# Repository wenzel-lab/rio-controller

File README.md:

# "Rio" the modular microfluidics controller 

This repository contains the _free_ and _open-source_ designs and documentation for the _core board_ and their _modules_ of a microfluidics workstation to enable _high-throughput droplet microfluidic_ biological assays. The designs contain an electronics board "hat" that plugs onto a Raspberry Pi single-board computer and interfaces with our _compact controllers_ e.g. for gas-pressure control to push microfluidic samples onto chips, pressure, and flow measurement with feedback control, sample holders with heating and stirring, and imaging of fast droplet generation processes with open-source microscopy and stroboscopic illumination.

This is an open, collaborative project by the [Wenzel Lab](https://wenzel-lab.github.io/en/) in Chile, and _your participation_ (comments, inputs, contributions) are explicitly welcome! Please submit your message as an issue in this repository to participate.

Follow us! [#twitter](https://twitter.com/WenzelLab), [#YouTube](https://www.youtube.com/@librehub), [#LinkedIn](https://www.linkedin.com/company/92802424), [#instagram](https://www.instagram.com/wenzellab/), [#Printables](https://www.printables.com/@WenzelLab), [#LIBREhub website](https://librehub.github.io), [#IIBM website](https://ingenieriabiologicaymedica.uc.cl/en/people/faculty/821-tobias-wenzel)

## Table of contents

- [Why](#why)
- [Getting Started](#getting-started)
- [Use Cases](#use-cases)
- [Read the Paper](#read-the-paper)
- [Modules Wish List](#modules-wish-list)
- [Contributing](#contributing)
- [License](#license)

## Why

Our aim is to create a prototype of a _compact_ working station for microfluidic research that is based on _connectable_, _open_, modern, and _low-cost_ components (Rasberry Pi, Arduino, 3D printing, on-board components, open or at least accessible design software and operation software - python).

**Rio** serves as a platform to implement fully functional research-grade workstations with good specifications, such as fast reaction times and low-pressure fluctuations. It is modular so that parts of this platform can be repurposed and improved in the open-source hardware sense and easily combined, exchanged, or used independently in challenging environments.

## Getting Started

For a repository architecture guide, see [ARCHITECTURE.md](ARCHITECTURE.md)
- **Software (runtime + development)**: [`software/README.md`](software/README.md)
  - Main entry point: `software/main.py`
- **Deployment bundle (Pi updates)**: generated via `scripts/deploy/create-pi-deployment.sh` into `pi-deployment/`
- **Hardware modules** (assembly + usage):
  - Pi HAT: [`hardware-modules/rpi-hat/README.md`](hardware-modules/rpi-hat/README.md)
  - Strobe imaging: [`hardware-modules/strobe-imaging/README.md`](hardware-modules/strobe-imaging/README.md)
  - Pressure/flow: [`hardware-modules/pressure-flow-control/README.md`](hardware-modules/pressure-flow-control/README.md)
  - Heating/stirring: [`hardware-modules/heating-stirring/README.md`](hardware-modules/heating-stirring/README.md)

In order to implement a workstation, you must build the core board and any module of your interest. The user interface software will allow you to control and monitor the operations of the modules.

### Core Board

The core board consists of a Raspberry Pi 4B+ and a custom Pi HAT (hardware attached to the top). The Pi HAT is an extension board for bidirectional communication and power supply to the controllers. 

<table>
<tr>
    <td align="center"><b>Core Board</b></td>
</tr>
<tr>
    <td align="center"></td>
</tr>
<tr>
    <td align="center"><a href="hardware-modules/rpi-hat/"><br><b>Build the Pi HAT</b></a><br><br></td>
</tr>
</table>

### Modules

A _module_ commonly consists of a compact controller, sensors, and actuators, and operates with distinct power supply and data connections. The controllers convert physical data into digital data, manipulate the actuators, and supply energy to external components. 

<table>
<tr>
    <td align="center"><b>Strobe Imaging Module</b></td>
    <td align="center"><b>Pressure and Flow Control Module</b></td>
    <td align="center"><b>Heat and Stirring Module</b></td>
</tr>
<tr>
    <td align="center"></td>
    <td align="center"></td>
    <td align="center"></td>
</tr>
<tr>
    <td align="center"><a href="hardware-modules/strobe-imaging/"><br><b>Build the controller</b></a><br><br></td>
    <td align="center"><a href="hardware-modules/pressure-flow-control/"><br><b>Build the controller</b></a><br><br></td>
    <td align="center"><a href="hardware-modules/heating-stirring/"><br><b>Build the controller</b></a><br><br></td>
</tr>
</table>

### Software

The software follows a client-server architecture and allows users to control the physical hardware through a graphical interface. It runs on a Raspberry Pi (legacy 32-bit OS for Pi camera support).

**Installation and Usage:**
- For detailed software installation and usage instructions, see [software/README.md](software/README.md)

**Features:**
- Real-time camera control with strobe synchronization
- Droplet detection with histogram visualization
- Flow and pressure control
- Temperature and stirring control
- Modern web-based user interface

**How the software is structured (high level):**
- UI + routes: `software/rio-webapp/` (browser + Flask + Socket.IO)
- WebSocket handlers: `software/rio-webapp/controllers/`
- Device orchestration: `software/controllers/`
- Hardware adapters: `software/drivers/` (camera backends in `software/drivers/camera/`)
- Droplet detection pipeline: `software/droplet-detection/`

### Choose Your Scenario

- **Scenario 1 — Pi image (UI on Pi, optional API)**: Flask UI autostarts on the Pi, API is optional.
- **Scenario 2 — Pi API-only + external UI/camera**: Pi exposes API for Pi-HAT modules; external computer runs UI + image processing.
- **Scenario 2b — Pi API-only + Pi camera via API**: legacy `picamera` remains on the Pi; clients control via API.

For Pi mode switching, use `scripts/pi/rio-mode` (UI vs API single-owner).

## Use Cases

**Single-module solution:**
* Strobe-enhanced microscopy stage ([Repository](https://github.com/wenzel-lab/strobe-enhanced-microscopy-stage) | [Assembly Instructions](https://wenzel-lab.github.io/strobe-enhanced-microscopy-stage/))

**Three-modules solution:**
* Flow microscopy platform ([Repository](https://github.com/wenzel-lab/flow-microscopy-platform) | Assembly Instructions (Soon))

## Read the Paper

"Rio" has been employed in the article ["Plasmid Stability Analysis with Open-Source Droplet Microfluidics"](https://app.jove.com/t/67659/plasmid-stability-analysis-with-open-source-droplet-microfluidics), published in JoVE in December 2024. Please cite this article when using our hardware system.

DOI: [https://dx.doi.org/10.3791/67659](https://dx.doi.org/10.3791/67659)

## Modules Wish List

* High-pressure source module to replace large gas bottles with a small soda CO2 bottle, developed in this [sub-repository](https://github.com/wenzel-lab/rio-controller/tree/master/module-high-pressure-source)
* Support for small piezo pumps
* Smart cultivation sleeves for vials, smaller and with OD-tracking - the V2 of our current sample holders and strirrers
* Microfluidic droplet sorting workstation driven by the droplet workstation tools is described [here](https://github.com/wenzel-lab/droplet-sorter-master/tree/main) (This is being developed in a separate repository).

## Contributing

Feel free to dive in! [Open an issue](https://github.com/wenzel-lab/rio-controller/issues/new).
For interactions in our team and with the community applies the [GOSH Code of Conduct](https://openhardware.science/gosh-2017/gosh-code-of-conduct/). If you want to get involved in our research, please see the [website of our team](https://wenzel-lab.github.io/en/).

## License

**Hardware:** All source files located in the `hardware-modules` directories (including firmware, PCB designs, and documentation) and documentation are released under the [CERN-OHL-W-2.0](https://ohwr.org/cern_ohl_w_v2.txt) license.

**Software:** The source codes located in the `software` directory are released under the [GPL-3.0](https://www.gnu.org/licenses/gpl-3.0.en.html) license.

© Tobias Wenzel, Christie Nel, and Pierre Padilla-Huamantinco. This project is Open-Source Hardware - please cite and acknowledge us when using the hardware or sharing modifications.

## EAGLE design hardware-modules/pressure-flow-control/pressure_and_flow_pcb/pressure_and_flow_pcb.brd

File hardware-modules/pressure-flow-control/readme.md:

## Pressure and flow controller module

This is the core piece of the workstation. 
This electronic controller module aims to regulate and distrbute the pressure (originating from the pressure source module) into the sample tubes, so that the samples (aqueous, gel pre-cursors and oils) flow onto the microfluidic chip and the collection reservoirs.
We regulate high pressure for ultra-high throughput agarose bead generation (several bar), in a smooth fashion that avoids pulsing, especially at steady state.
This controller consists of a custom circuit board that plugs into the Raspberry Pi hat, in addition to connectors for connecting external pressure controllers and flow sensors. Pressure and flow control are fully automatic.

The controller module can operate either in pressure control mode or flow control mode.  Flow control mode requires external flow sensors to be connected.  Once desired flow rates have been achieved and associated pressures are known, the experiment can be reproduced using only pressure control, without the need for expensive flow sensors.  Both modes require external pressure controllers to be connected.

The module contains a PIC microcontroller that communicates with the Raspberry Pi, controls the pressure controllers and reads back pressure and flow.  The pressure target is controlled using a digital-to-analogue converter and the actual pressure is read using an analogue-to-digital converter.  The flow controllers is read via a four channel I2C multiplexer.

### Where the firmware and software live (repo structure)

- **Module firmware (PIC, MPLAB X project)**: `pressure_and_flow_pic/`
  - Developer-oriented firmware notes: `pressure_and_flow_pic/README.md`
- **Host-side driver (Raspberry Pi)**: `software/drivers/flow.py` (`PiFlow`)
- **UI-facing controller wrapper**: `software/controllers/flow_web.py` (`FlowWeb`)
- **UI wiring (web app)**: `software/rio-webapp/` + `software/rio-webapp/controllers/flow_controller.py`

When auditing end-to-end behavior, the most direct call chain is:
browser UI → Socket.IO `"flow"` handler → `FlowWeb` → `PiFlow` → `pressure_and_flow_pic/` firmware.

### Pressure Controllers
We have selected the SMC ITV0010 pressure controllers for this application.  The pressure target is supplied to the pressure controller by the module as an analogue voltage and the measured pressure achieved is returned as an analogue voltage.  This approach allows the option to connect alternative analogue pressure controllers, or using a separate pressure sensor instead of the one internal to the pressure controller.

The ITV0010 pressure controllers can be purchased as a compact DIN-mounted manifold block that requires a single pressure supply line.

### Flow Sensors
We have selected the Sensirion LG16 range of flow sensor.  They feature a digital interface via I2C.

### Connectors

The module features eight Picoblade connectors.  Four connect to the pressure controllers, carrying power, analogue out and analogue in.  The other four connect to the optional flow sensors and carry power and I2C signals.  The module itself is designed to plug into the Raspberry Pi hat.  This allows for power and digital communications with the Raspberry Pi.

#### Pressure Controller Connector

|Pin|Description|
|-|-|
|1|Pressure In|
|2|Pressure Out|
|3|0V Power / GND|
|4|12V Power|

#### Flow Sensor Connector

|Pin|Description|
|-|-|
|1|I2C Data|
|2|Vdd 3.3V|
|3|Vss (Digital Ground)|
|4|I2C Clock|

**Note:** Pin 2 (Vdd 3.3V) must not be used to power Sensirion LG16 sensors, which require 5V.  This 3.3V pin was intended for use with the Sensirion SLF3S-1300F.  Instead use the 5V pin on the Controller Module header block on the Raspberry Pi hat.

### Pinout

|Pin|Description|
|-|-|
|1|ICSP MCLR|
|2|ICSP Vdd (3V3 Power)|
|3|ICSP Vss (Digital Ground)|
|4|ICSP Data|
|5|ICSP Clock|
|13|Ground for 12V|
|14|12V Supply for Pressure Controllers|
|17|5V Digital Power|
|23|Digital Ground|
|24|Digital 3.3V Power|
|25|SPI Slave Select|
|26|SPI Clock|
|27|SPI MOSI|
|28|SPI MISO|

**Note:** Pin 13 (12V Ground) must be connected with pin 23 (digital ground) externally, and in a way that prevents ground loops.

### PCB Components

|Qty|Name|Component|Description|
|-|-|-|-|
|7|C1-C5,C8-C9|100nf Capacitor 0603|Decoupling Capacitors|
|2|C6,C10|10uF Capacitor 0603|Bypass,Bulk Capacitor|
|1|C7|Not fitted||
|1|IC2|dsPIC33CK256MP502-I/SS SSOP28|PIC Microprocessor|
|1|IC3|AD5624R|DAC|
|1|IC4|ADS1115|ADC|
|1|IC5|PCA9544APW,112|I2C Multiplexer|
|1|IC6|25AA040ST|EEPROM|
|12|R1-R10,R12-R13|1k Resistor 0603||
|1|R11|10k Resistor 0603||
|8|X1-X8|Picoblade 53047-0410|Connectors|

Please note that our current implementation is based on compact, low-cost and scalable PIC microcontrollers that fit onto the Pi-hat modules. These cannot simply be programmed with a micro-USB cables. Instead, they need an [additional small hardware ICSP interface](https://www.digikey.com/en/product-highlight/m/microchip-technology/pickit-3-in-circuit-debugger-programmer) (or equivalent) to load new code onto the PIC microcontrollers.

### Cable for Sensirion LG16

Flow Controller Module End

Connector Type: Picoblade 1.25mm 4-way (51021-0400)<br/>
Connector Crimps: Picoblade 26-28 AWG (50079-8000)

|Pin|Wire|Function|
|-|-|-|
|1|1|I2C Data|
|2|-|Not Connected|
|3|3|VSS|
|4|4|I2C Clock|

Connector Type: DuPont Standard Female

|Pin|Wire|Function|
|-|-|-|
|1|2|VDD 5V|

Flow Sensor End (Sensirion LG16)

Connector Type: Picoblade 1.25mm 5-way (51021-0500)<br/>
Connector Crimps: Picoblade 26-28 AWG (50079-8000)

|Pin|Wire|Function|
|-|-|-|
|1|1|I2C Data|
|2|4|I2C Clock|
|3|2|VDD 5V|
|4|3|VSS|
|5|-|Not Connected|

### Cable for SMC ITV Electro-Pneumatic Regulator

This cable was purchased from bpx.co.uk and a Picoblade connector fitted, which plugs into the Flow Controller Module.  The wires are too thick to fit directly into the crimps, so thinner wires must be soldered onto the cable.

Cable: M84DSX3MG4<br/>
Connector Type: Picoblade 1.25mm 4-way (51021-0400)<br/>
Connector Crimps: Picoblade 26-28 AWG (50079-8000)

|Pin|Colour|Function|
|-|-|-|
|1|Black|Input Signal|
|2|White|Monitor Output|
|3|Blue|GND (Common)|
|4|Brown|Power|

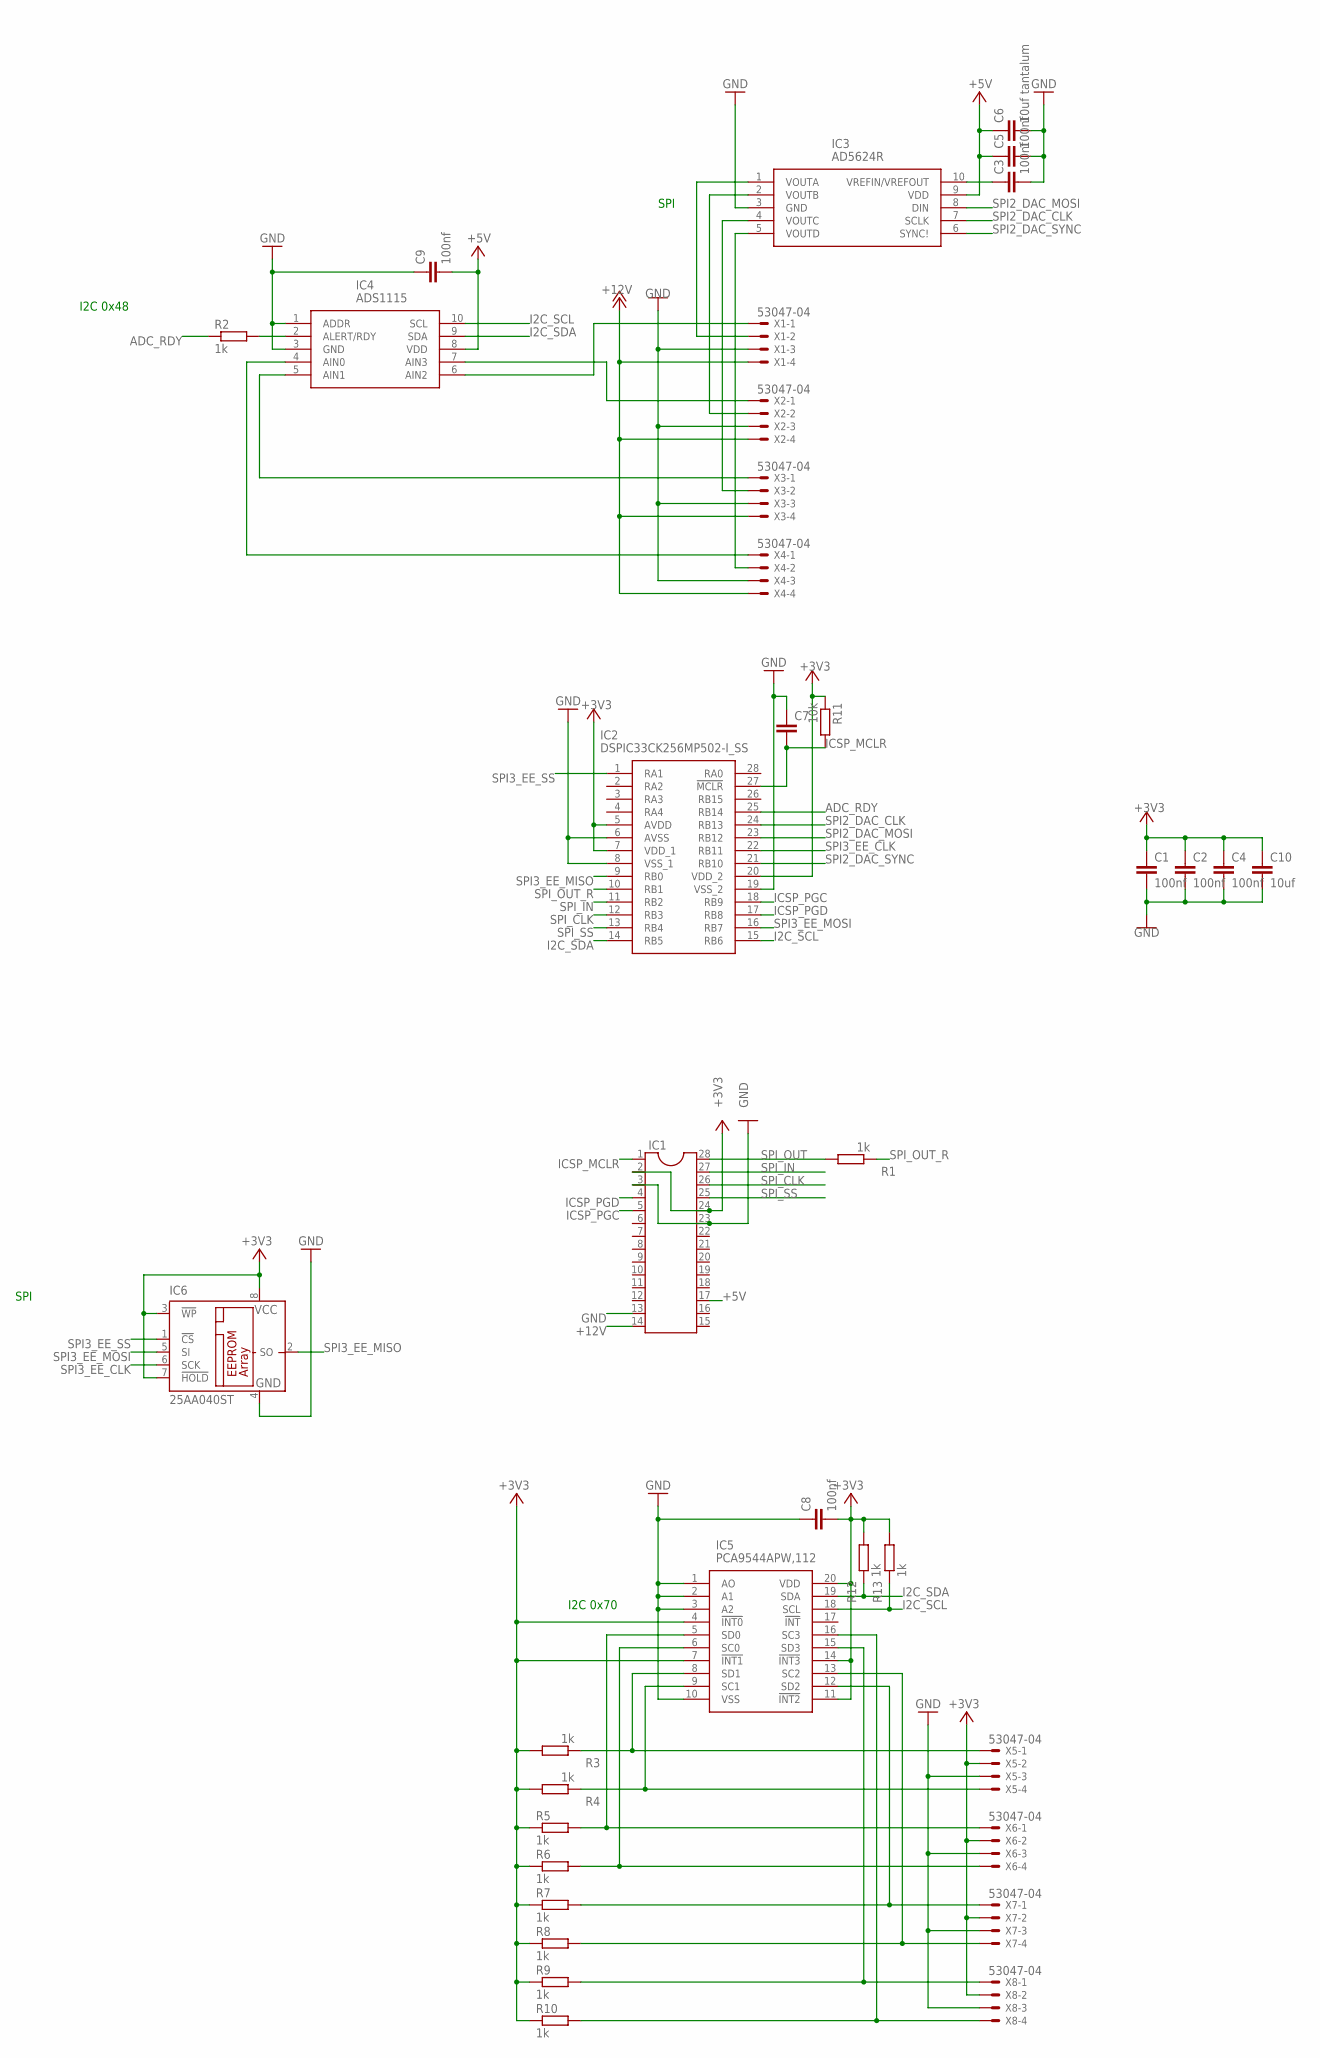
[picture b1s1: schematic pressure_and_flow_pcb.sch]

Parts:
C1, C2, C3, C4, C5, C8, C9: 100nf; C0603K
C6: 10uf tantalum; C0603K
C7: C-EUC0603K; C0603K
C10: 10uf; C0603K
IC1: DIL28; DIL28-6
IC2: DSPIC33CK256MP502-I_SS; SOP65P780X200-28N
IC3: AD5624R; SOP50P490X110-10N
IC4: ADS1115; SOP50P490X110-10N
IC5: PCA9544APW,112; SOP65P640X110-20N
IC6: 25AA040ST; TSSOP8
R1, R2, R3, R4, R5, R6, R7, R8, R9, R10, R12, R13: 1k; R0603
R11: 10k; R0603
X1, X2, X3, X4, X5, X6, X7, X8: 53047-04

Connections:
+3V3: C1.1, C2.1, C4.1, C8.2, C10.1, IC1.2, IC1.24, IC2.5 (AVDD), IC2.7 (VDD_1), IC2.20 (VDD_2), IC5.4 (!INT0), IC5.7 (!INT1), IC5.11 (!INT2), IC5.14 (!INT3), IC5.20 (VDD), IC6.3 (!WP), IC6.7 (!HOLD), IC6.8 (VCC), R3.2, R4.2, R5.1, R6.1, R7.1, R8.1, R9.1, R10.1, R11.1, R12.2, R13.2, X5.2, X6.2, X7.2, X8.2
+5V: C5.1, C6.1, C9.2, IC1.17, IC3.9 (VDD), IC4.8 (VDD)
+12V: IC1.14, X1.4, X2.4, X3.4, X4.4
ADC_RDY: IC2.25 (RB14), R2.1
GND: C1.2, C2.2, C3.2, C4.2, C5.2, C6.2, C7.1, C8.1, C9.1, C10.2, IC1.3, IC1.13, IC1.23, IC2.6 (AVSS), IC2.8 (VSS_1), IC2.19 (VSS_2), IC3.3 (GND), IC4.1 (ADDR), IC4.3 (GND), IC5.1 (AO), IC5.2 (A1), IC5.3 (A2), IC5.10 (VSS), IC6.4 (GND), X1.3, X2.3, X3.3, X4.3, X5.3, X6.3, X7.3, X8.3
I2C_CLK: IC5.9 (SC1), R4.1, X5.4
I2C_DATA: IC5.8 (SD1), R3.1, X5.1
I2C_SCL: IC2.15 (RB6), IC4.10 (SCL), IC5.18 (SCL), R13.1
I2C_SDA: IC2.14 (RB5), IC4.9 (SDA), IC5.19 (SDA), R12.1
ICSP_MCLR: C7.2, IC1.1, IC2.27 (!MCLR), R11.2
ICSP_PGC: IC1.5, IC2.18 (RB9)
ICSP_PGD: IC1.4, IC2.17 (RB8)
unnamed: C3.1, IC3.10 (VREFIN/VREFOUT)
unnamed: IC3.2 (VOUTB), X2.2
unnamed: IC3.4 (VOUTC), X3.2
unnamed: IC4.2 (ALERT/RDY), R2.2
unnamed: IC4.5 (AIN1), X3.1
unnamed: IC3.5 (VOUTD), X4.2
unnamed: IC5.5 (SD0), R5.2, X6.1
unnamed: IC5.6 (SC0), R6.2, X6.4
unnamed: IC5.12 (SD2), R7.2, X7.1
unnamed: IC5.13 (SC2), R8.2, X7.4
unnamed: IC5.15 (SD3), R9.2, X8.1
unnamed: IC5.16 (SC3), R10.2, X8.4
unnamed: IC4.7 (AIN3), X2.1
unnamed: IC4.4 (AIN0), X4.1
PRESSURE_IN: IC4.6 (AIN2), X1.1
PRESSURE_OUT: IC3.1 (VOUTA), X1.2
SPI2_DAC_CLK: IC2.24 (RB13), IC3.7 (SCLK)
SPI2_DAC_MOSI: IC2.23 (RB12), IC3.8 (DIN)
SPI2_DAC_SYNC: IC2.21 (RB10), IC3.6 (SYNC!)
SPI3_EE_CLK: IC2.22 (RB11), IC6.6 (SCK)
SPI3_EE_MISO: IC2.9 (RB0), IC6.2 (SO)
SPI3_EE_MOSI: IC2.16 (RB7), IC6.5 (SI)
SPI3_EE_SS: IC2.1 (RA1), IC6.1 (!CS)
SPI_CLK: IC1.26, IC2.12 (RB3)
SPI_IN: IC1.27, IC2.11 (RB2)
SPI_OUT: IC1.28, R1.2
SPI_OUT_R: IC2.10 (RB1), R1.1
SPI_SS: IC1.25, IC2.13 (RB4)

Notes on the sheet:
I2C 0x48
SPI
I2C 0x70

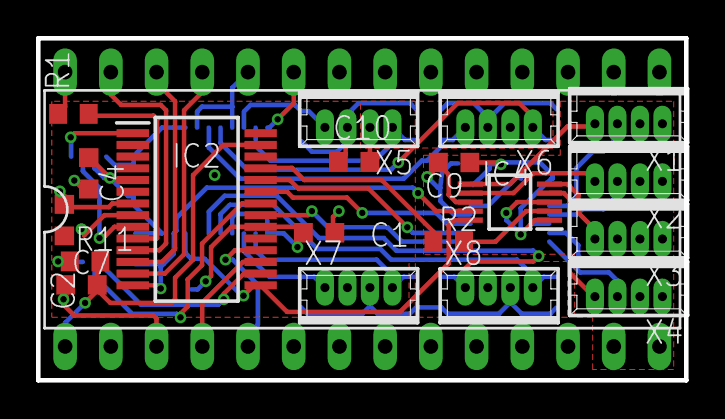
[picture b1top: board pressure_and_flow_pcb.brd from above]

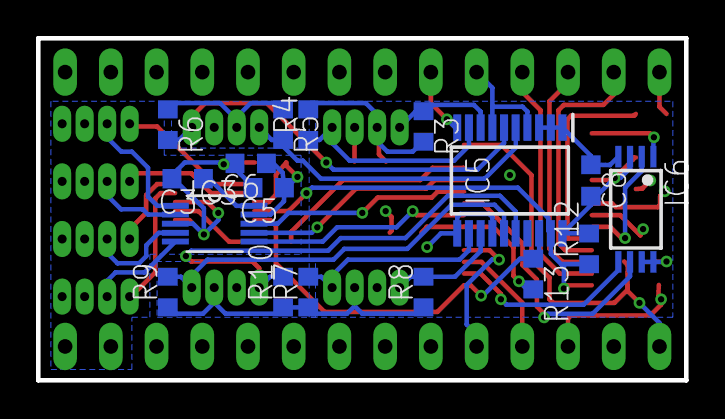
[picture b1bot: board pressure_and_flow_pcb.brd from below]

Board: 4 copper layers, 36.0 x 19.0 mm, 37 parts (17 on the bottom side), 40 nets.

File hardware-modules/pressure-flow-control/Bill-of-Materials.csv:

Item #,Ref Des,Full Name/Description,Category,Part/Catalog Number,Manufacturer/Supplier,Notes
7,C1-C5;C8-C9,100nf Capacitor 0603,Electronics,,,Decoupling Capacitors
2,C6;C10,10uF Capacitor 0603,Electronics,,,Bypass / Bulk Capacitor
1,C7,Not fitted,Electronics,,,
1,IC2,PIC Microprocessor,Electronics,dsPIC33CK256MP502-I/SS SSOP28,Microchip,
1,IC3,DAC,Electronics,AD5624R,Analog Devices,
1,IC4,ADC,Electronics,ADS1115,Texas Instruments,
1,IC5,I2C Multiplexer,Electronics,PCA9544APW;112,NXP,
1,IC6,EEPROM,Electronics,25AA040ST,Microchip,
12,R1-R10;R12-R13,1k Resistor 0603,Electronics,,,
1,R11,10k Resistor 0603,Electronics,,,
8,X1-X8,Connectors,Electronics,Picoblade 53047-0410,Molex,
8,,Picoblade 1.25mm 4-way,Cables,51021-0400,Molex,
4,,Picoblade 1.25mm 5-way,Cables,51021-0500,Molex,
52,,Picoblade 26-28 AWG Crimps,Cables,50079-8000,Molex,
4,,DuPont Standard Female 1-Way,Cables,,,Ubiquitous
4,,SMC ITV Cable,Cables,M84DSX3MG4,SMC,
4,,SL Male 4-Way Connector,Cables,70107-0038,Molex,Enclosure Connectors (Actuators)
4,,SL Female 4-Way Connector,Cables,50-57-9404,Molex,Enclosure Connectors (Actuators)
4,,SL Male 5-Way Connector,Cables,70107-5039,Molex,Enclosure Connectors (Flow Sensor)
4,,SL Female 5-Way Connector,Cables,50-57-9405,Molex,Enclosure Connectors (Flow Sensor)
36,,SL Male Crimps,Cables,16-02-0105,Molex,
36,,SL Female Crimps,Cables,16-02-0069,Molex,

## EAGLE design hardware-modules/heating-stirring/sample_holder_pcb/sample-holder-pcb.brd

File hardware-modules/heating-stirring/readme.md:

# Heating and stirring module

The sample holder is used to heat microfluidic sample liquids such as water, oil or agarose to a set temperature and optionally stirring the sample using a magnetic stir bar, before pumping it through a microfluidics chip.  The PCB can also be used separately with external heaters to heat tubing or microscope glass slides.

The sample holder module comprises a PCB, two cartridge heaters, temperature sensor and stirring motor and magnets, all integrated into an aluminium shell.  Aluminium inserts that slot into the top can be machined to accommodate sample bottles of various shapes and sizes.  The sample holder connects to a Raspberry Pi via SPI, from which the sample holder temperature and stir speed are set and monitored.

The sample holder has been tested to 100 degrees Celcius and provides a stable (but uncalibrated) readout to 0.01 degrees Celcius.

## PCB

The sample holder PCB is the heart of the sample holder and contains a PIC microprocessor that reads the temperature sensor, controls the heaters and stirrer motor and offers an SPI interface to a host.

The PCB has been designed for dual use.  It can be mounted in a sample holder with heaters, temperature sensor and stir motor wires soldered to the PCB.  Alternatively, it can also be used with external heater and temperature sensor attached via the secondary connector as shown below.

The connector on the left is the primary connector and provides 12V power for the heaters, 3.3V power for the microprocessor and SPI communications with the Raspberry Pi.

The connector on the right is the secondary connector that connects to the external heater (black wires) and temperature sensor (white wires).  The polarity of heater and temperature sensor does not matter.  The connector also provides debug serial output and ICSP interface for reprogramming the PIC microprocessor.

### PCB Primary Connector : Power and SPI Interface

|Pin|Description|
|-|-|
|1|SPI Clock|
|2|SPI Slave Select|
|3|Vdd 3.3V|
|4|SPI MOSI|
|5|Vss (Digital Ground)|
|6|SPI MISO|
|7|Heater 0V|
|8|Heater 12V|
|9|Heater 0V|
|10|Heater 12V|

**Note:** Vss(GND) must be connected with Heater 0V, and in a way that prevents ground loops.

### PCB Secondary Connector : External Heater, Temperature Sensor, Debug Serial and Programming Interface (ICSP)

|Pin|Description|
|-|-|
|1|Heater Out 12V|
|2|ICSP MCLR|
|3|Heater Out 0V|
|4|ICSP 3.3V|
|5|Temp Sensor (Vss)|
|6|ICSP GND (Vss)|
|7|Temp Sensor +|
|8|ICSP PGD|
|9|Serial Debug TX|
|10|ICSP PGC|

**Note:** Do not supply ICSP 3.3V while also supplying Vdd 3.3V as they are connected.

### PCB FET Mounting

A power FET is mounted on the bottom of the PCB and drives the heaters.  It is intended to touch the metal the PCB is mounted on, with thermal paste between FET and metal.

### PCB Components

|Qty|Name|Component|Description|
|-|-|-|-|
|1|IC2|dsPIC33CK256MP502-I/SS SSOP28|PIC Microprocessor|
|1|IC1|25AA128-I/ST TSSOP8|SPI EEPROM|
|1|Q1|AUIRFU8403 IPAK|MOSFET|
|2|T1,T3|MMBT3904LT1 SOT23|NPN Transistor|
|2|T2,T4|MMBT3906LT1 SOT23|PNP Transistor|
|1|LED1|LTST-S270KGKT 0603|Green Side View LED|
|2|J1,J2|10 Pin 2 Row Angled Header||
|1|R7|3.3k Resistor|Temperature Sensor Reference|
|6|R1-R6|1k Resistor 0603||
|1|R9|10k Resistor 0603|PIC MCLR Pull Up|
|1|R8|120R Resistor 0603|LED Resistor|
|4|C1,C2,C4,C6|100nf Capacitor 0603|Decoupling Capacitors|
|1|C3|1nf Capacitor 0603|Motor Drive Capacitor|
|1|C5|10uf Capacitor 1206|Bulk Capacitor|

Please note that our current implementation is based on compact, low-cost and scalable PIC microcontrollers that fit onto the Pi-hat modules. These cannot simply be programmed with a micro-USB cables. Instead, they need an [additional small hardware ICSP interface](https://www.digikey.com/en/product-highlight/m/microchip-technology/pickit-3-in-circuit-debugger-programmer) (or equivalent) to load new code onto the PIC microcontrollers.  

## Heaters and Sensors

The heaters are 3.3 Ohm (rated 12V, 40W) stainless steel cartridges that insert into holes drilled into the top section of the sample holder.  A temperature sensor is inserted into a hole drilled into the same section.  The temperature sensor is a negative coefficient thermister (NTC).  These heaters and temperature sensors are commonly used in 3D printers and can be found on eBay or Amazon.

## Stirrer Motor and Magnets

The stirrer motor rotates two attached magnets, which in turn rotate an optional stirrer magnet in the sample bottle inserted into the top of the sample holder.

The stirrer motor is a standard 40mm x 40mm x 10mm, three wire fan.  The rotating side points upward and has two 6mm diameter x 2mm thick Neodymium magnets mounted flat next to each other (opposing poles same side) in the centre of the fan.  The magnets have to be raised off the fan such that their fields do not interfere with the operation of the fan, be close enough to the stirrer magnet, while not touching the opposing surface.  We find that raising it 3-4mm with layers of double sided tape is sufficient and provides enough strength to spin the stirrer magnet.  The fan wire colours are typically black=ground, red=12V, yellow=sense/tachometer.

## Power Considerations

The heaters can draw quite a lot of power, so an adequate 12V power supply must be provided.  At full power with two 3.3 Ohm heaters, the required current can be calculated as:
I = ( 12V / 3.3 Ohm ) * 2 heaters = 7.3A
The maximum power can be limited by storing a power limit percentage to the sample holder via SPI.  Alternatively, these 40W heater cartridges are also made for 24V, which have around 4x the resistance (P=V^2/R, 40=24^2/R, R=14.4 Ohm) and will thus consume 1/4 as much power, but heat more slowly.

## Mechanical Design

The sample holder is constructed from layers of machined 54mm diameter aluminium rod as listed in the table below.  The overall dimensions and screw locations are determined by the 40mm fan used as a stir motor.

|Section|Description|
|---|---|
|Top|The top section houses the two heater cartridges and temperature sensor and is the part that gets hot.  It also houses an insert that is shaped to fit a particular sample vessel.|
|Insulation|A layer of FR4 material that insulates the heated top from the rest of the module.|
|Magnet Space|A cavity above the motor/fan where the stir magnets rotate.|
|Motor|The stir motor that rotates the stir magnets.|
|PCB Mount|The plate that the PCB is mounted on with standoffs.  This plate also used as a heatsink for the FET that protrudes from the PCB.|
|PCB Spacer|The cavity for the PCB and wires.|
|Bottom|The bottom plate that closes up the PCB cavity and also holds the screw heads.|

[Download Mechanical Design PDF](doc/sample_holder_design.pdf)

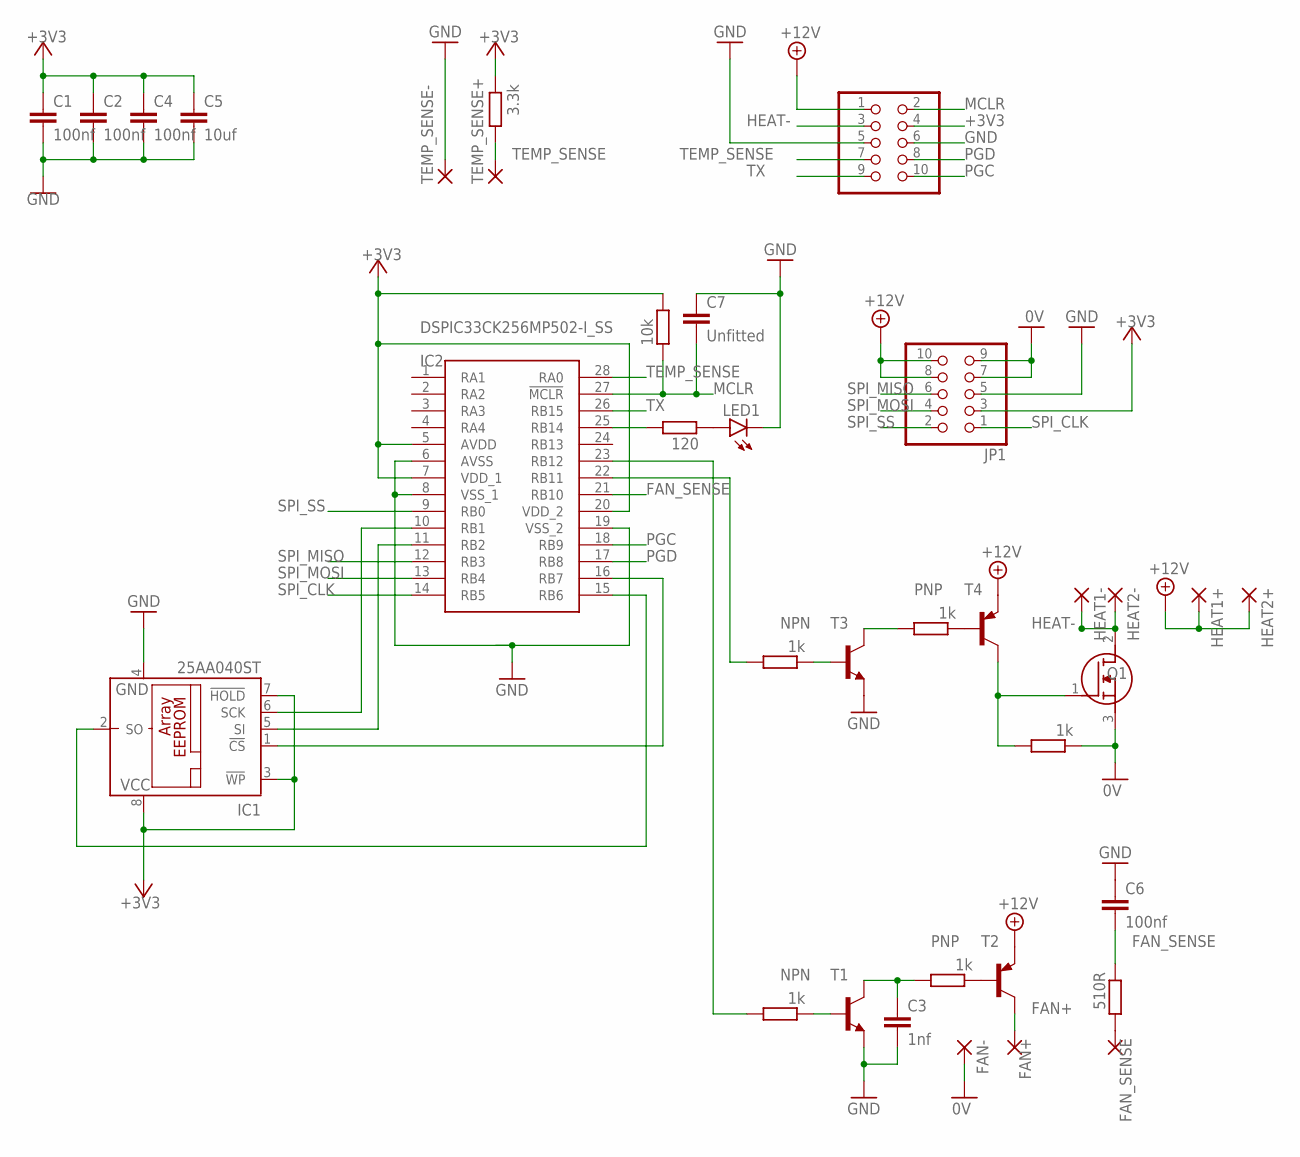
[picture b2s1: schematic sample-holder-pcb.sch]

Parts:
C1, C2, C4, C6: 100nf; C0603
C3: 1nf; C0603
C5: 10uf; C1206
C7: Unfitted; C0603
FAN+: 1,6/0,8
FAN-: 1,6/0,8
FAN_SENSE: 1,6/0,8
HEAT1+, HEAT1-, HEAT2+, HEAT2-: 2,54/1,0
IC1: 25AA040ST; TSSOP8
IC2: DSPIC33CK256MP502-I_SS; SOP65P780X200-28N
JP1, JP2: PINHD-2X5/90; 2X05/90
LED1: LEDSML0603; SML0603
Q1: AUIRFU8403; TO229P239X654X978-3P
R1, R2, R3, R4, R5: 1k; R0603
R6: 510R; R0603
R7: 3.3k; R0603
R8: 120; R0603
R9: 10k; R0603
T1, T3: NPN; SOT23-BEC
T2, T4: PNP; SOT23-BEC
TEMP_SENSE+: 1,6/0,8
TEMP_SENSE-: 1,6/0,8

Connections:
0V: FAN-.1, JP1.7, JP1.9, Q1.3 (S), R5.1
+3V3: C1.1, C2.1, C4.1, C5.1, IC1.3 (!WP), IC1.7 (!HOLD), IC1.8 (VCC), IC2.5 (AVDD), IC2.7 (VDD_1), IC2.20 (VDD_2), JP1.3, JP2.4, R7.1, R9.1
+12V: HEAT1+.1, HEAT2+.1, JP1.8, JP1.10, JP2.1, T2.E, T4.E
FAN+: FAN+.1, T2.C
FAN_SENSE: C6.2, IC2.21 (RB10), R6.1
GND: C1.2, C2.2, C3.2, C4.2, C5.2, C6.1, C7.1, IC1.4 (GND), IC2.6 (AVSS), IC2.8 (VSS_1), IC2.19 (VSS_2), JP1.5, JP2.5, JP2.6, LED1.C, T1.E, T3.E, TEMP_SENSE-.1
HEAT-: HEAT1-.1, HEAT2-.1, JP2.3, Q1.2 (D)
MCLR: C7.2, IC2.27 (!MCLR), JP2.2, R9.2
unnamed: R2.1, T3.B
unnamed: R4.2, T3.C
unnamed: R4.1, T4.B
unnamed: Q1.1 (G), R5.2, T4.C
unnamed: FAN_SENSE.1, R6.2
unnamed: LED1.A, R8.2
unnamed: IC2.25 (RB14), R8.1
unnamed: R1.1, T1.B
unnamed: C3.1, R3.2, T1.C
unnamed: R3.1, T2.B
unnamed: IC2.22 (RB11), R2.2
unnamed: IC1.5 (SI), IC2.11 (RB2)
unnamed: IC1.6 (SCK), IC2.10 (RB1)
unnamed: IC1.2 (SO), IC2.15 (RB6)
unnamed: IC1.1 (!CS), IC2.16 (RB7)
unnamed: IC2.23 (RB12), R1.2
PGC: IC2.18 (RB9), JP2.10
PGD: IC2.17 (RB8), JP2.8
SPI_CLK: IC2.14 (RB5), JP1.1
SPI_MISO: IC2.12 (RB3), JP1.6
SPI_MOSI: IC2.13 (RB4), JP1.4
SPI_SS: IC2.9 (RB0), JP1.2
TEMP_SENSE: IC2.28 (RA0), JP2.7, R7.2, TEMP_SENSE+.1
TX: IC2.26 (RB15), JP2.9

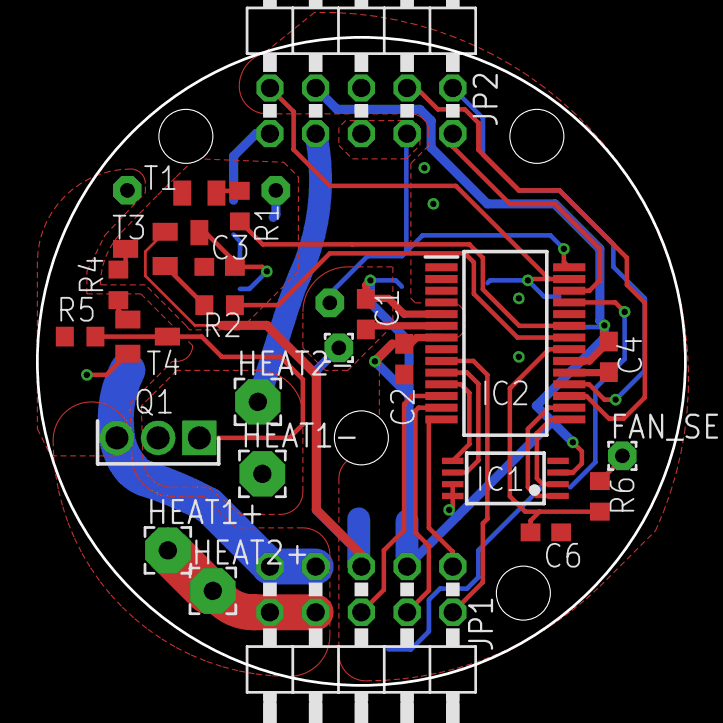
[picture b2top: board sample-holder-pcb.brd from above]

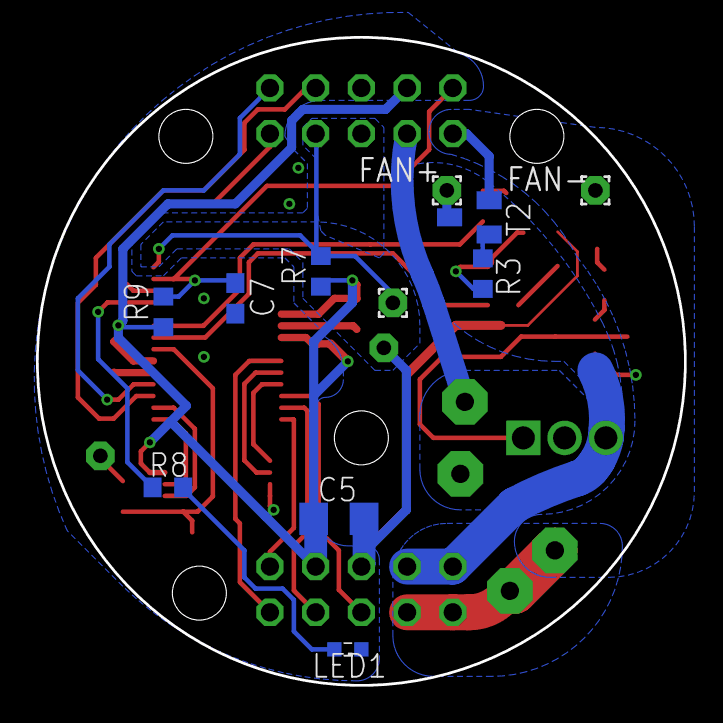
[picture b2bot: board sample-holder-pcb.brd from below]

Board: 2 copper layers, 36.0 x 36.0 mm, 35 parts (11 on the bottom side), 32 nets.

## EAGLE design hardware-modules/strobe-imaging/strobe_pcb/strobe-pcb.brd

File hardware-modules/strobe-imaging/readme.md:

# Strobe Imaging Module

Stroboscopic imaging is an interesting technique that 'freezes' the motion of fast-moving objects. The light source needs to be synchronized with the objects to be inspected, and the camera is triggered at the exact moment of the light pulse. 

The _**Strobe Imaging Module**_ integrates a controller, sensor, and actuator for imaging fast processes, particularly developed for microfluidic droplet generation.

* The _sensor_ is a Raspberry Pi camera V2, a CMOS sensor with an 8-megapixel resolution. If higher technical specifications are required, the module is compatible with the MAKO U-029 high-speed camera.
* The _actuator_ consists of a high-power LED attached to a heat sink and assembled with a condenser lens to transmit light through the samples, which is collected by the _sensor_.
* The _controller_ is a PIC microcontroller board that handles the instant activation of the _actuator_ to capture sharp images of fast moving objects with the _sensor_. It activates the _actuator_ at a specific frequency, defined by the frame rate and exposure time of the _sensor_.

## Features

* High-intensity stroboscopic illumination.
* Two optical configurations: low-cost (Pi lens) and RMS (standard objetives) versions.
* Compatible with industrial high-speed cameras.
* Open-source firmware

## Manufacturing and Assembly

### 1. [Bill of Materials](Bill-of-Materials.csv)

### 2. Required Tools:

<details>
<summary><strong>For assembly</strong></summary>

* Crimper
* Needle-nose plier
* Precision wire cutter
* Soldering iron (with fine tip)
* Soldering wire
* Flux
* Tweezer
* Magnifying tool
* PCB holder or third hand
* Multimeter
* Optional: Soldering paste, tip cleaner, desoldering pump, hot air rework station
</details>

<details>
<summary><strong>For programming</strong></summary>

* MPLAB X IDE v6.10
* XC8 compiler
* USB Drivers of PIC programmer
* PICkit3 programmer (Microchip)
* Mini USB to USB cable
* [Programming cable]() (to connect the PIC programmer to the strobe controller)
</details>

### 3. Programming of Controller:

<details>
<summary><strong>STEP 1: Physical Connection</strong></summary>

Connect the [programming cable]() to the PIC programmer. The green wire would connect to the pin with the white label.

The other end of the cable connects to the first five pins on the controller, which are the five bottom-left pins as seen from above.

The green wire would connect to the bottom left pin. There should also be a marking on the cable connector by the green wire to confirm it is pin 1.  Please do take care to plug it in the right way.

The controller pins are not mapped one-to-one to the chip. You can plug the cable straight onto the controller pins - no need for jumpers.

Color Cable | Programmer Pin | PIC Pin |
------------|----------------|---------|
Green       | MCRL           | PIN 1 (MCLR) |
Brown       | VDD            | PIN 20 (VDD) |
White       | GND/VSS        | PIN 8 (VSS) |
Orange      | PGD            | PIN 28 (ICSPDAT) |
Blue        | PGC            | PIN 27 (ICSPCLK) |

</details>

<details>
<summary><strong>STEP 2: PIC programming</strong></summary>

You will have to download MPLAB X, which might take a while. Then, open the [strobe_pic project](strobe_pic/) in MPLAB X.

Around the top left of MPLAB X, you will see a box where you can select different configurations. Select the **PICkit3** configuration.

Under the **Projects** tab, right click on the [strobe_pic project](strobe_pic/) and select **Properties**.

On the top right, change the device to **PIC16F18856**.

The next step is important. If you plug straight into the controller, the PICkit3 programmer needs to provide power to it. Under **Conf: PICkit3**, select **PICkit 3**.  Under **Option categories:** select **Power** and check the box. Press OK.

Click the "Clean and Build" button.

If the configuration is correct, MPLAB X will report **BUILD SUCCESSFUL** in the text box at the bottom.

Make sure everything is connected. Use the Mini USB to USB cable to connect the PIC programmer with the computer.

Click the **Program** button.

It might ask you to select the PICkit3 and might then download the latest firmware to it.

If it says something about reading the wrong ID from the PIC, something is wrong with your connections or soldering (ID 0x0000 or 0xFFFF) or you have a different PIC (if a different ID).

</details>

### 4. Assembly of Sensor:

### 5. Assembly of Actuator:

### 6. Assembly of Custom Cables:

<details>
<summary><strong>Programming cable</strong></summary>

</details>

<details>
<summary><strong>Strobe cable</strong></summary>

</details>

## Usage

### Requirements

* The core board (a Raspberry Pi 4B+ and the [Pi HAT](../../rpi-hat/)) with the [user interface software](../../software/)
* Computer peripherals: monitor, keyboard, and mouse 
* 5V/3A power supply
* Power splitter cable (to supply power to the core board and actuator)
* Voltage regulator (the actuator works with 3V) 

### Schematic of a single-module setup

In the figure below, the schematic representation shows the module, the core board, and (A) low-cost and (B) RMS optical configurations.   

### Use case

The _Strobe Imaging Module_ has been employed in the implementation of a strobe-enhanced microscopy stage for training and research ( [Repository](https://github.com/wenzel-lab/strobe-enhanced-microscopy-stage) | [Assembly Instructions](https://wenzel-lab.github.io/strobe-enhanced-microscopy-stage/) ).

## Results

**1. Microchannels visualization:**
By using the lens of the Raspberry Pi camera (A), the module presents a 1 mm field of view (FOV) with a working distance of approximately 5 mm. The magnification of this optical configuration is comparable to a 4X objective (B), offering a broad FOV to monitor channel behavior, flow patterns, or droplet generation. 

<br>

**2. Droplet generation in a microfluidic chip (Objective: 4X):**
The image below shows (A) sequential images captured at different stages of droplet formation using the module to verify imaging capabilities for monitoring droplet generation. (B) By zooming in a section of the microfluidic channel, droplets can be easily distinguished from the surrounding oil and qualitatively verify the uniformity in droplet size. The intensity plot demonstrates it showing a consistent drop in grayscale values within the droplet boundary.

<br>

**3. Static and moving droplets (Objective: 4X):**
Water-in-oil droplets were generated under varying continuous phase (Qc) and dispersed phase (Qd) flow rates and imaged with the module. Droplet size and uniformity can be monitored as well as droplet generation dynamics. 

<br>

**4. Droplet generation and droplet splitting (Objective: 4X)**

## Design Criteria

For detailed information about the design decisions and camera approach selection, see [design-criteria.md](design-criteria.md).

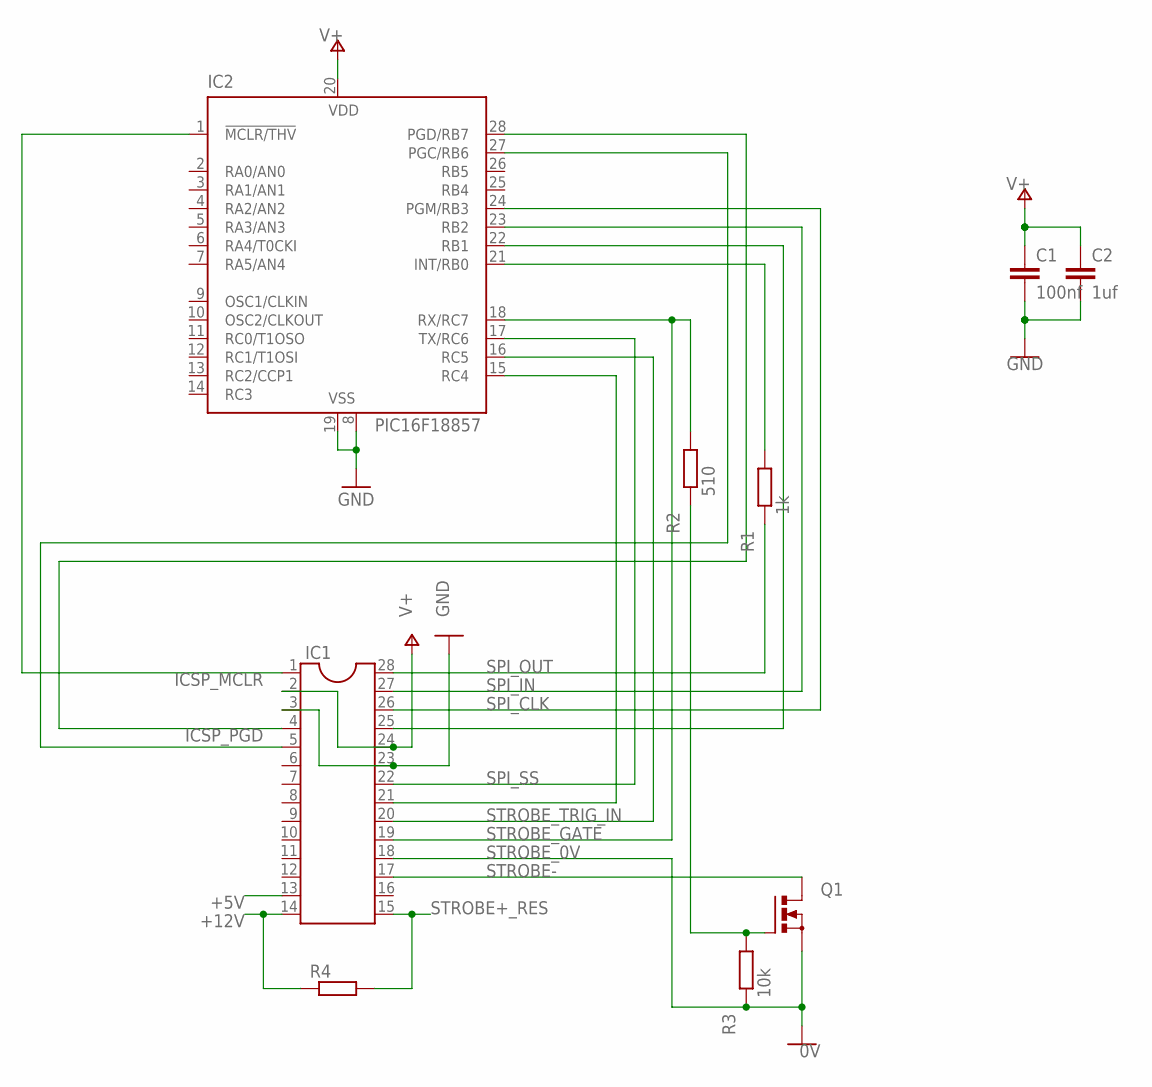
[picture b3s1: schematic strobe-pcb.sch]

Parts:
C1: 100nf; C1206
C2: 1uf; C1206
IC1: DIL28; DIL28-6
IC2: PIC16F18857; SO28W
Q1: PMOSFET_NTO220BV; TO220BV
R1: 1k; R1206
R2: 510; R1206
R3: 10k; R1206
R4: R-EU_0207/10; 0207/10

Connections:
+5V: IC1.13
+12V: IC1.14, R4.1
GND: C1.2, C2.2, IC1.3, IC1.23, IC2.8 (VSS), IC2.19 (VSS)
ICSP_MCLR: IC1.1, IC2.1 (!MCLR/THV)
ICSP_PGD: IC1.4, IC2.28 (PGD/RB7)
unnamed: IC1.25, IC2.22 (RB1)
unnamed: IC2.21 (INT/RB0), R1.2
unnamed: IC1.5, IC2.27 (PGC/RB6)
unnamed: Q1.G, R2.1, R3.2
unnamed: IC1.21, IC2.15 (RC4)
SPI_CLK: IC1.26, IC2.24 (PGM/RB3)
SPI_IN: IC1.27, IC2.23 (RB2)
SPI_OUT: IC1.28, R1.1
SPI_SS: IC1.22, IC2.17 (TX/RC6)
STROBE+_RES: IC1.15, R4.2
STROBE-: IC1.17, Q1.D
STROBE_0V: IC1.18, Q1.S, R3.1
STROBE_GATE: IC1.19, IC2.18 (RX/RC7), R2.2
STROBE_TRIG_IN: IC1.20, IC2.16 (RC5)
V+: C1.1, C2.1, IC1.2, IC1.24, IC2.20 (VDD)

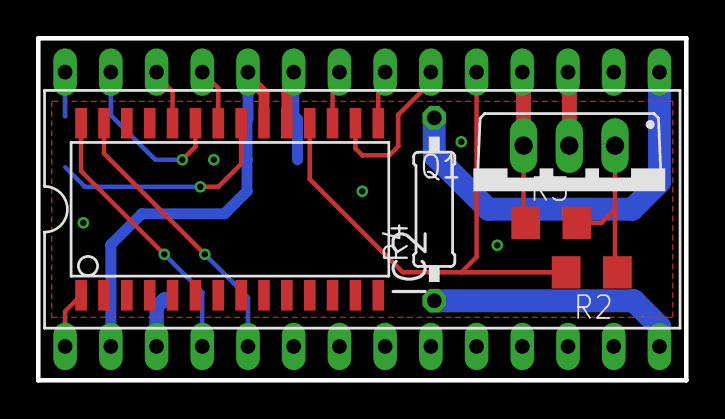
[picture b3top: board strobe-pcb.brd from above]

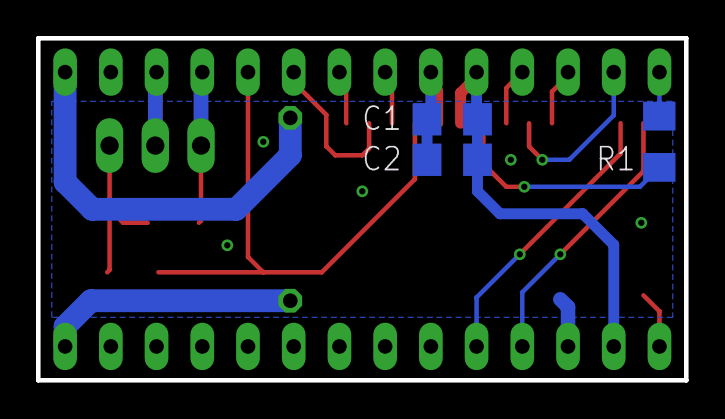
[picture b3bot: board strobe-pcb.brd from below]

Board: 2 copper layers, 36.0 x 19.0 mm, 9 parts (3 on the bottom side), 19 nets.
